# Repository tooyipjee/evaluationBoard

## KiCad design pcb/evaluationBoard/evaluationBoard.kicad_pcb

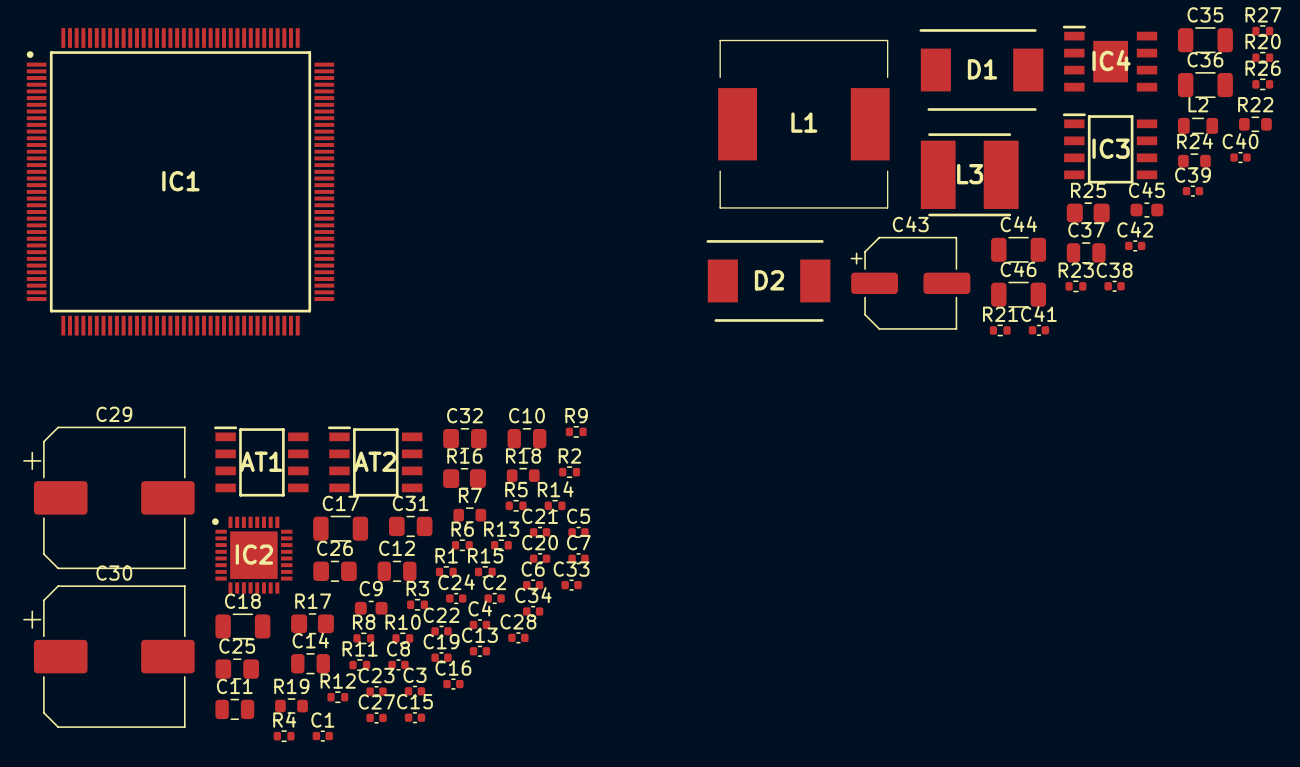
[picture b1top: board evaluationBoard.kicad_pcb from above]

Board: 2 copper layers, 84 parts (0 on the bottom side), 60 nets, no tracks yet.

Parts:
AT1, AT2: LM386MX-1_NOPB; SOIC127P600X175-8N
C1, C6, C7, C8: 33p; C_0402_1005Metric
C2, C3, C4, C5, C13, C15, C16, C21, C22, C23, C24, C33, C34, C39: 100n; C_0402_1005Metric
C9: 1u; C_0603_1608Metric
C10, C11, C12, C14, C37: 10u; C_0805_2012Metric
C17, C18, C44, C46: 47uF; C_1206_3216Metric
C19, C20: 4.7n; C_0402_1005Metric
C25, C26, C31, C32: NA_C; C_0805_2012Metric_Pad1.18x1.45mm_HandSolder
C27, C28: 47n; C_0402_1005Metric
C29, C30: 220uF_E; CP_Elec_10x10
C35, C36: 4.7u; C_1206_3216Metric
C38, C40, C41: 10n; C_0402_1005Metric
C42: 1n; C_0402_1005Metric
C43: 220uF_E; CP_Elec_6.3x7.7
C45: 47pF; C_0603_1608Metric
D1, D2: SS34; DIOM8059X256N
IC1: STM32F429ZGT6; QFP50P2200X2200X160-144N
IC2: TLV320AIC3254IRHBT; QFN50P500X500X100-33N-D
IC3: TPS54331DR; SOIC127P600X175-8N
IC4: TPS5430DDAR; SOIC127P600X170-9N
L1: 15uH; SWRB1204S150MT
L2: 3.3uH; L_0805_2012Metric
L3: 6.8uH; INDPM6060X450N
R1, R2, R3, R4, R8, R9, R10: 22; R_0402_1005Metric
R5, R6, R11, R12, R14, R15: 1k; R_0402_1005Metric
R7, R18, R19: 10; R_0603_1608Metric
R13: 2.7k; R_0402_1005Metric
R16, R17: NA_R; R_0805_2012Metric_Pad1.20x1.40mm_HandSolder
R20: 330k; R_0402_1005Metric
R21: 68k; R_0402_1005Metric
R22: 30k; R_0603_1608Metric
R23, R26: 10k; R_0402_1005Metric
R24: 3k; R_0603_1608Metric
R25: 0; R_0805_2012Metric_Pad1.20x1.40mm_HandSolder
R27: 3.3k; R_0402_1005Metric

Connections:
+3V3: C9.1, C11.1, C13.1, C44.1, C46.1, IC2.6, IC2.26, IC2.30, L3.2, R25.1
+5V: C43.1, L2.2, R23.1
+VDC: C35.1, C36.1, C37.1, C38.1, IC3.2, IC4.7, R20.1
/dsp/-IN1_L: C2.2, R11.2
/dsp/-IN1_R: C3.2, R12.1
/dsp/-IN2_L: C4.2, R5.2
/dsp/-IN2_R: C5.2, R6.1
/dsp/LOL: IC2.22, R14.2
/dsp/LOR: IC2.23, R15.2
/dsp/MIC+: C16.1, IC2.8, R13.2
GND: AT1.4, AT2.4, C1.2, C6.2, C7.2, C8.2, C9.2, C10.2, C11.2, C12.2, C13.2, C14.2, C19.2, C20.2, C22.2, C24.2, C27.2, C28.2, C31.1, C32.1, C33.1, C34.1, C35.2, C36.2, C37.2, C38.2, C40.2, C43.2, C44.2, C45.2, C46.2, D1.2, D2.2, IC2.7, IC2.12, IC2.17, IC2.28, IC2.33, IC3.7, IC4.6, IC4.9, R6.2, R12.2, R21.2, R22.2, R24.2, R27.2
MICBIAS: IC2.19, R5.1, R11.1, R13.1
unnamed: AT1.1, R16.2
unnamed: AT1.2, C21.1
unnamed: AT1.3, C22.1
unnamed: AT1.5, C29.1, R18.1
unnamed: AT1.7, C31.2
unnamed: AT1.8, C25.1
unnamed: AT2.1, R17.2
unnamed: AT2.2, C23.1
unnamed: AT2.3, C24.1
unnamed: AT2.5, C30.1, R19.1
unnamed: AT2.7, C32.2
unnamed: AT2.8, C26.1
unnamed: C1.1, C2.1, IC2.13
unnamed: C3.1, C6.1, IC2.14
unnamed: C4.1, C7.1, IC2.15
unnamed: C5.1, C8.1, IC2.16
unnamed: C10.1, C12.1, C14.1, IC2.18, IC2.24, IC2.29
unnamed: C15.2, IC2.20
unnamed: C16.2, IC2.21
unnamed: C17.2, IC2.25
unnamed: C18.2, IC2.27
unnamed: C19.1, C21.2, R14.1
unnamed: C20.1, C23.2, R15.1
unnamed: C25.2, R16.1
unnamed: C26.2, R17.1
unnamed: C27.1, R18.2
unnamed: C28.1, R19.2
unnamed: C39.1, D2.1, IC3.8, L3.1
unnamed: C39.2, IC3.1
unnamed: C40.1, IC3.4
unnamed: C41.1, D1.1, IC4.8, L1.1
unnamed: C41.2, IC4.1
unnamed: C42.1, C45.1, IC3.6
unnamed: C42.2, R22.1
unnamed: IC2.1, R7.1
unnamed: IC2.2, R1.1
unnamed: IC2.3, R8.1
unnamed: IC2.4, R2.1
unnamed: IC2.5, R9.1
unnamed: IC2.9, R3.1
unnamed: IC2.10, R10.1
unnamed: IC2.11, R4.1
unnamed: IC3.3, R20.2, R21.1
unnamed: IC3.5, R26.2, R27.1
unnamed: IC4.4, R23.2, R24.1
unnamed: L1.2, L2.1
unnamed: R25.2, R26.1
VDC: AT1.6, AT2.6, C33.2, C34.2

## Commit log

2021-01-07 datasheets
2021-01-07 Added IC components
2021-01-08 power schematic completed
2021-01-11 updated design
2021-05-26 added modules
